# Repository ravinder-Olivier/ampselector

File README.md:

# Ampselector (Guitar Rig 7 centric macropad)

Ampselector is a 8 key + two encoder macropad designed to be used for Guitar Rig 7. For actions such as switching between amps or effects presets.

Built using a RP2040 microcontroller in the form of the SEEED STUDIO XIAO, and powered by custom software built on QMK.

## Features: 
- 4x2 grid array
- Dual EC11 microcontrollers
- OLED Display
- Natively outputs MIDI CC codes, and can be programmed into GR7

## CAD / Assembly
- The PCB is screwed *(M3 screw)* onto the lower case with two screws *(into heatset inserts)*
- The top panel is super glued onto the lower case *(sleeker look)*
- Uses MX style keys and keycaps
- This was designed in Fusion360
- Make sure to flash firmware and have it running before you superglue the case together!

(note that usb port cutout is not visible in the first image)

## PCB 
- I would recommend buying a thicker style of 2 layer PCB for this project, for the added durability and rigidity
- This was designed in KiCad 

## BILL OF MATERIALS (BOM)
This project uses:
- 1x Seeed Studio XIAO RP2040
- 8x through hole 1N4148 diodes
- 1x OLED Display (.91in)
- 2x EC11 Rotarary Encoders
- 8x MX Style Keyswitches
- 8x DSA Keycaps
- 2x M3 x 16mm Screws
- 2x M3 Heatset inserts
- 1x PCB (order with gerbers.zip in production)
- 1x Top case (3d print  file in production)
- 1x Bottom case (3d print  file in production)

## Flashing firmware:
- Download the "firmware.uf2" file
- Press and hold the BOOT button on the RP2040 board
- Connect the Data compatible USB cable to the board
- It will appear like a USB drive on your computer, drop the "firmware.uf2" file onto it
- Once it uploads it should disappear as a USB drive, and restart and begin running the QMK firmware!

## Mapping to Guitar Rig 7:
- The keyboard will output various MIDI CC codes, which you can map to various functions in GR7. There's some good info on this forum [thread](https://community.native-instruments.com/discussion/46400/guitar-rig-7-switching-presets-live-with-a-midi-foot-controller)

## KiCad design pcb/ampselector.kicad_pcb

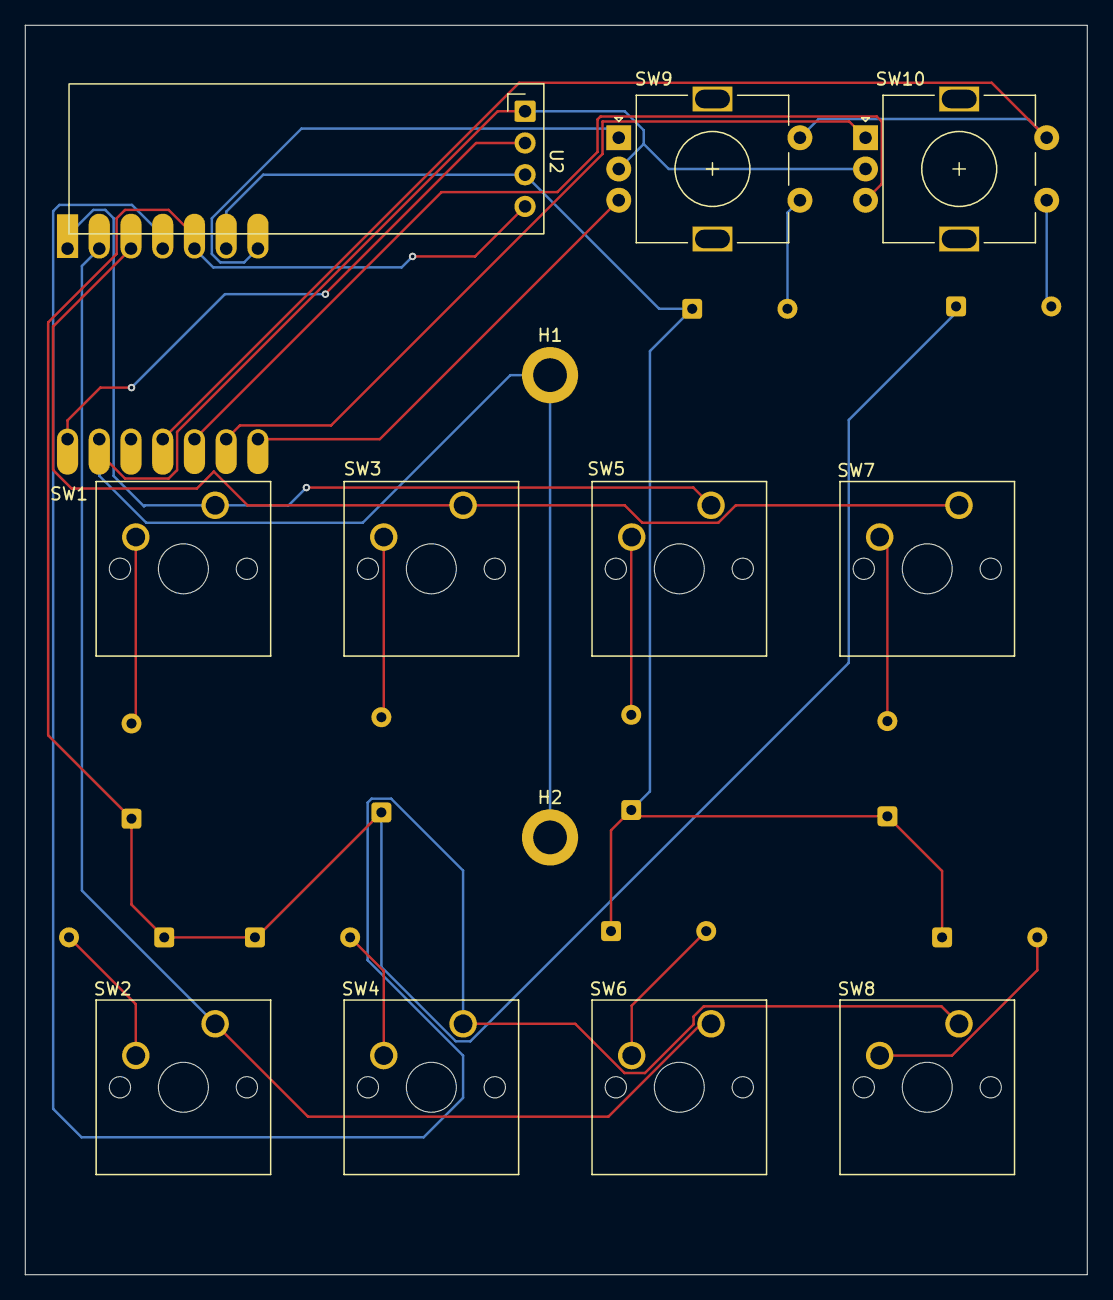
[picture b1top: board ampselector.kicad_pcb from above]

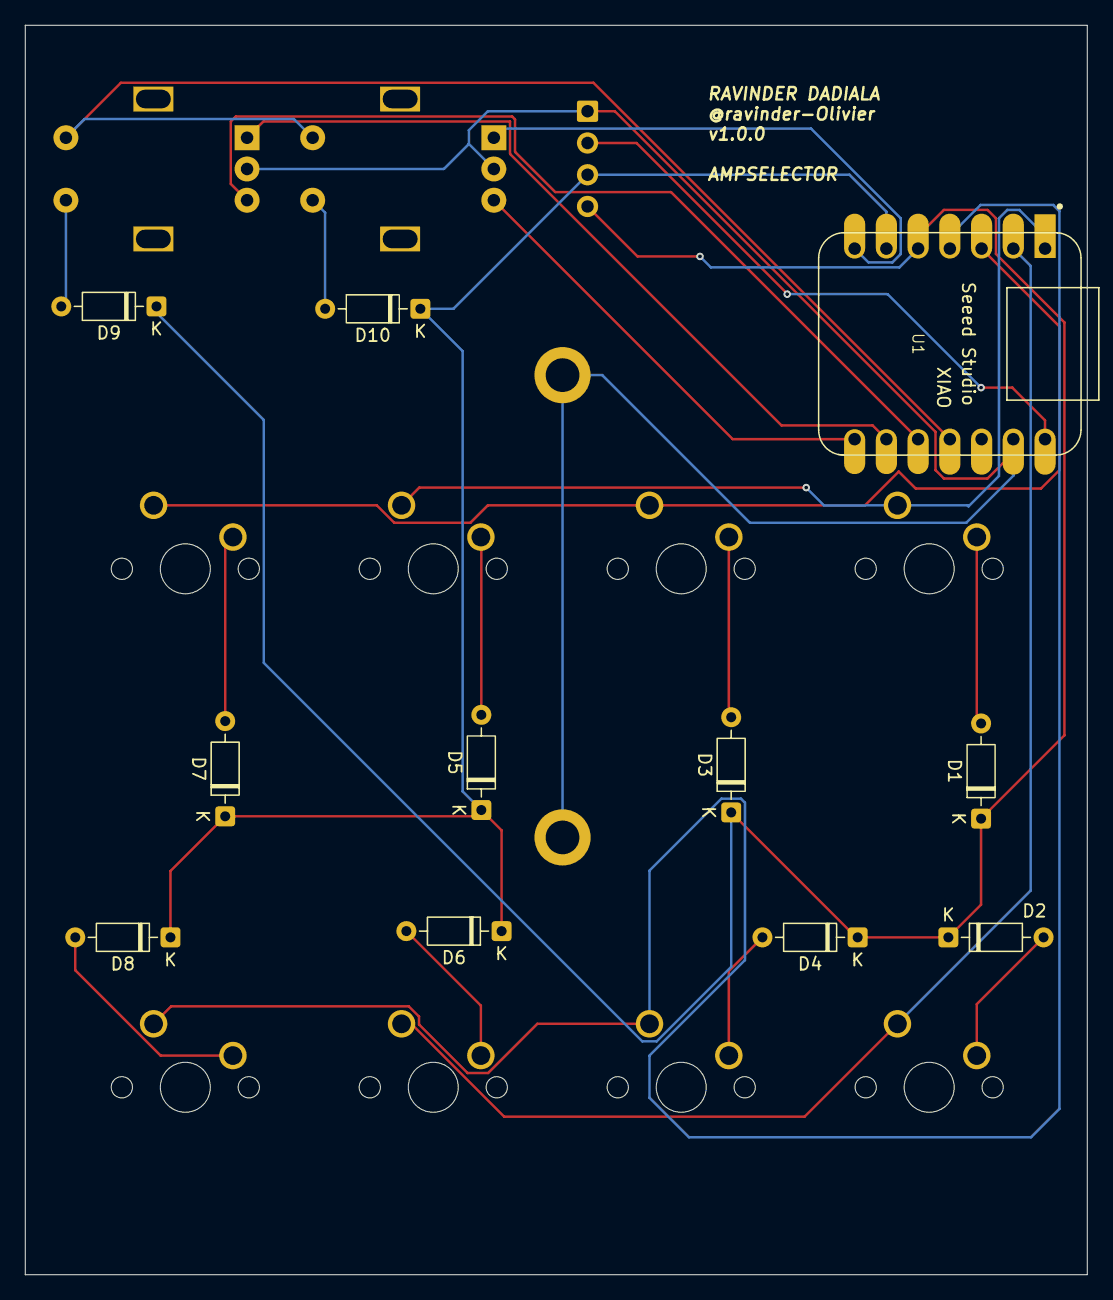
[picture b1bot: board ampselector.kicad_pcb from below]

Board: 2 copper layers, 85.0 x 100.0 mm, 24 parts (11 on the bottom side), 23 nets.

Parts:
D1, D2, D3, D4, D5, D6, D7, D8, D9, D10: 1N4148; D_DO-35_SOD27_P7.62mm_Horizontal
H1, H2: MountingHole_Pad; MountingHole_2.7mm_M2.5_ISO7380_Pad
SW1, SW2, SW3, SW4, SW5, SW6, SW7, SW8: SW_Push; SW_Cherry_MX_1.00u_PCB
SW9, SW10: RotaryEncoder_Switch; RotaryEncoder_Alps_EC11E-Switch_Vertical_H20mm
U1: MOUDLE-SEEEDUINO-XIAO; XIAO-Generic-Hybrid-14P-2.54-21X17.8MM
U2: ER_OLEDM0.91_1x-I2C

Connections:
GND: H1.1 (1_1), H2.1 (1_1), SW9.C, SW10.C, U1.13 (GND), U2.1 (GND)
unnamed: D1.2 (A), SW1.2
unnamed: D1.1 (K), D2.1 (K), D3.1 (K), D4.1 (K), D9.1 (K), U1.5 (PA8_A4_D4_SDA), U2.4 (SDA)
unnamed: D2.2 (A), SW2.2
unnamed: D3.2 (A), SW3.2
unnamed: D4.2 (A), SW4.2
unnamed: D5.2 (A), SW5.2
unnamed: D6.2 (A), SW6.2
unnamed: D7.2 (A), SW7.2
unnamed: D8.2 (A), SW8.2
unnamed: D9.2 (A), SW10.S1
unnamed: D10.2 (A), SW9.S1
unnamed: D5.1 (K), D6.1 (K), D7.1 (K), D8.1 (K), D10.1 (K), U1.6 (PA9_A5_D5_SCL), U2.3 (SCL)
unnamed: SW1.1, SW5.1, U1.1 (PA02_A0_D0)
unnamed: SW2.1, SW6.1, U1.2 (PA4_A1_D1)
unnamed: SW10.B, U1.10 (PA5_A9_D9_MISO)
unnamed: SW9.S2, SW10.S2, U1.11 (PA6_A10_D10_MOSI)
unnamed: SW10.A, U1.9 (PA7_A8_D8_SCK)
unnamed: SW3.1, SW7.1, U1.3 (PA10_A2_D2)
unnamed: SW4.1, SW8.1, U1.4 (PA11_A3_D3)
unnamed: SW9.A, U1.7 (PB08_A6_D6_TX)
unnamed: SW9.B, U1.8 (PB09_A7_D7_RX)
VCC: U1.14 (5V), U2.2 (VCC)

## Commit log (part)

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2026-06-13 Format
2026-06-13 Folder org
2026-06-13 added gitignore
2026-06-13 Initialize README with project details and images
    Added project description and PCB format images to README.
2026-06-13 keyboard firmware basic
2026-06-13 gitignore update
2026-06-13 keyboard map done
2026-06-13 minimal updates
2026-06-13 fixed incorrect pins for matrix wiring
2026-06-14 fixing qmk errors
2026-06-14 bootloader
2026-06-14 qmk functional
2026-06-14 encoder map func
2026-06-14 qmk updates
2026-06-14 UPDATED PIN REFERENCES
2026-06-16 updated kc codes
2026-06-16 instructions for installing firmware
2026-06-16 Update README.md
    update readme
2026-06-17 Designed Case
2026-06-17 production/dir updates
2026-06-17 Exported gerbers.zip
2026-06-17 Added silkscreen
2026-06-17 Add Bill of Materials to README
    Added a Bill of Materials section listing required components for the project.
2026-06-17 Updated folder structure to be suitable
2026-06-18 MAJOR SILKSCREEN FIX
2026-06-18 Updated preset for kicanvas
2026-06-20 changed text layer on silkscreen
2026-06-20 Integrating midi in config files
2026-06-20 implemented oled and full midi control
2026-06-20 minor oled update
2026-06-20 format update
2026-06-20 firmware update
2026-06-24 Build instructions added
2026-06-27 Added BOM
